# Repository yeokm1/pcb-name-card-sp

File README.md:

# pcb-name-card-sp

My name or business card that is on a Printed Circuit Board (PCB). Comes with an white LED, UV LED and a ruler. Not forgetting a QR code containing my contact details in [Vcard](https://en.wikipedia.org/wiki/VCard) format. This is an update to my [previous version](https://github.com/yeokm1/pcb-name-card) since I have changed my company.

### PCB Design software and addons/references used

1. Eagle 8.0.2
2. Modified CR2032 library based on [here](https://github.com/nickaknudson/eagle-nickaknudson/blob/master/cr2032.lbr)
2. Elecrow Design Rule Check for 2 layers (in repo as `Elecrow_2-layer_eagle_rule.dru`)
3. Elecrow Gerber Generater 2-layer board (in repo as `Elecrow_Gerber_Generater_DrillAlign.cam`)
4. QR code generated from [here](http://goqr.me/)

### Schematic drawings

Image are exported from Eagle at 600dpi.

The board schematic as seen in Eagle. The connections are slightly convoluted to prevent the traces from crossing in the board layout.

### Bill of Materials (BOM) for components only

Assume minimum order 10 pieces, cost in Singapore dollars. There are additional savings if I order more say 50 units but the savings are still small. Delivery for BOM not included.

The BOM is available in the odt spreadsheets in this repo.

### PCB fabrication

PCB fabrication is currently done by [Elecrow (10-pieces-link)](http://www.elecrow.com/10pcs-2-layer-pcb-p-1175.html) or [(50-pieces-link)](http://www.elecrow.com/50pcs-2-layer-pcb-enig-p-1172.html) based on the following settings. Remember to consult the order submission specifications at the bottom of the previous link before submitting. Use the provided Gerber generator to produce the Gerber files.

#### My Fabrication Settings:

1. Layer: 2
2. PCB Thickness: 0.6mm
3. Copper Weight : 1oz 35um (NA for 50 pieces)
4. PCB Size : 10cm Max * 10cm Max (or 50cm2 for 50 pieces)
5. PCB Color : Blue
6. Surface Finish: ENIG
7. PCB Stencil : NO Stencil
8. Lead time : Shipped in 4 to 7 days (NA for 50 pieces)
9. Panelizing : Single PCB with milling

# References
1. [How to design a 13.56 MHz
customized tag antenna](http://www.st.com/st-web-ui/static/active/jp/resource/technical/document/application_note/CD00221490.pdf)
2. [The impact of high pulse drain on CR2032 coin-cell battery capacity](http://m.eet.com/media/1121454/c0924post.pdf)
3. [Panasonic NFC Design Navigator](http://www.semicon.panasonic.co.jp/en/tool/nfcdesignnavigator/)

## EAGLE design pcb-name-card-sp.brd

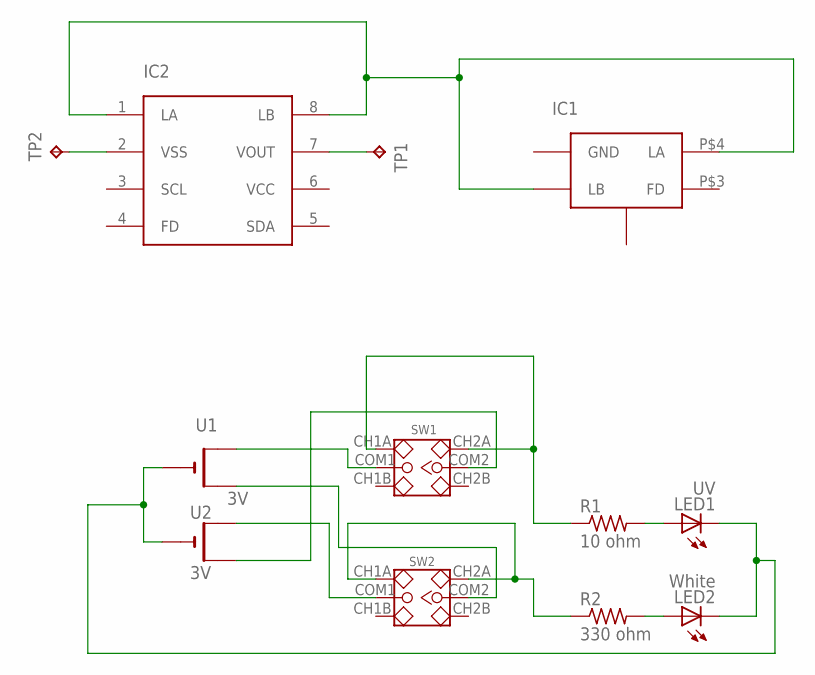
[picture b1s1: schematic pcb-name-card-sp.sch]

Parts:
IC1: NTAG21XFDRC-FIT; HXSON4-SMALL
IC2: NT3H1X01W0FTT; TSSOP-8
LED1: UV; PLCC2
LED2: White; PLCC2
R1: 10 ohm; R2010
R2: 330 ohm; R2010
SW1, SW2: SMD-TOGGLE-SWITCH-2CH(2X3P-7X3.5MM); SW6-2.54-SMD-7.0X3.5X1.5MM
TP1: VOUT; B2,54
TP2: GND; B2,54
U1, U2: 3V; CR2032-SMD

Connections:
unnamed: LED1.A, R1.2
unnamed: LED2.A, R2.2
unnamed: R2.1, SW2.CH1A, SW2.CH2A
unnamed: IC1.P$2 (LB), IC1.P$4 (LA), IC2.1 (LA), IC2.8 (LB)
unnamed: LED1.C, LED2.C, U1.-, U2.-
unnamed: SW1.COM1, U1.+$1 (+)
unnamed: IC2.2 (VSS), TP2.TP
unnamed: IC2.7 (VOUT), TP1.TP
unnamed: SW2.COM1, U2.+$1 (+)
unnamed: SW2.COM2, U1.+$2 (+1)
unnamed: SW1.COM2, U2.+$2 (+1)
unnamed: R1.1, SW1.CH1A, SW1.CH2A

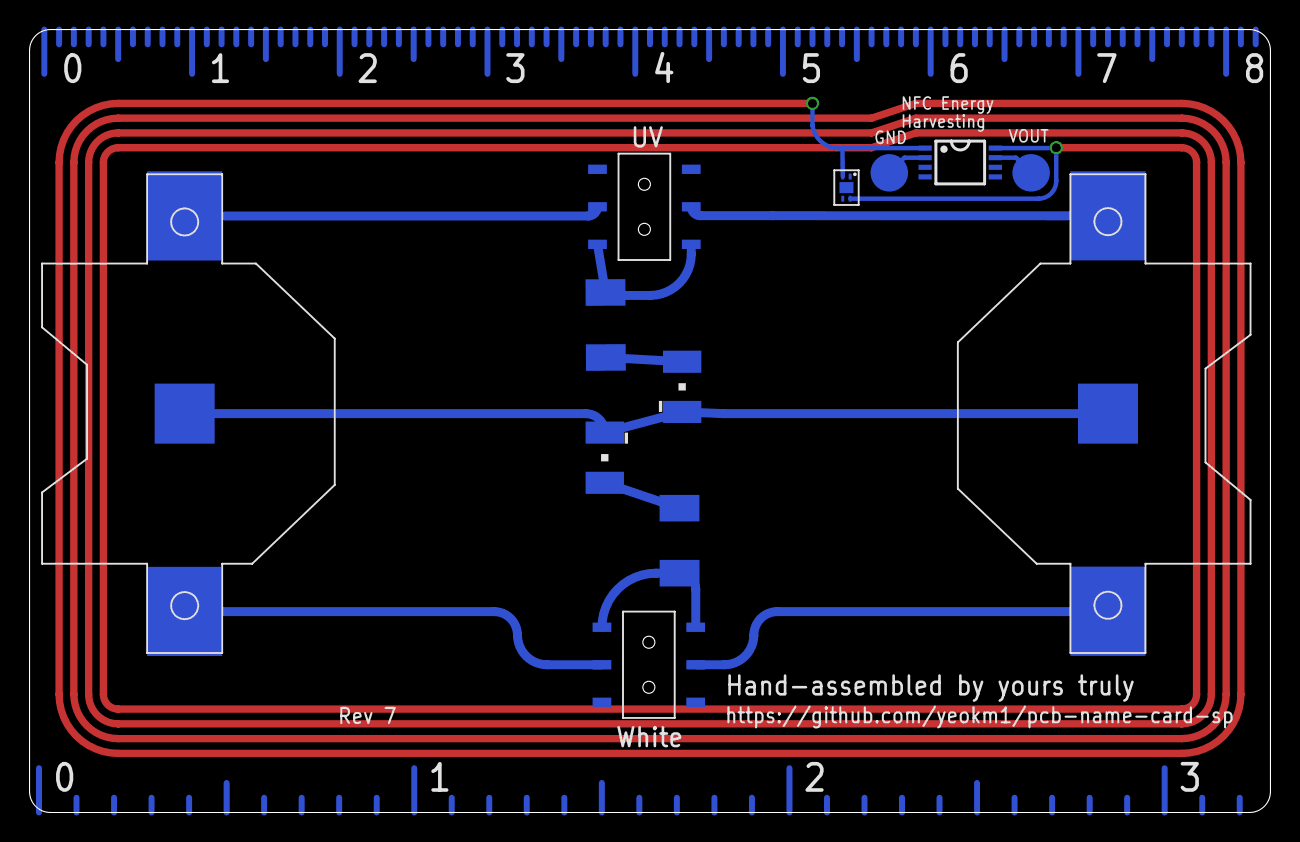
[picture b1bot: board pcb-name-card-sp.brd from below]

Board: 2 copper layers, 84.0 x 53.0 mm, 12 parts (12 on the bottom side), 12 nets.

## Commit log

2017-02-18 new card rebranded design
2017-02-18 show all layers
2017-02-18 rev2 gerber
2017-02-21 Adjusted logo position
2017-02-21 rev3 gerber
2017-02-28 add www to spgroup url
2017-03-02 rev5 moves close to actual sp card
2017-03-11 readme with new image
2017-05-17 slides
2018-08-11 update new job title
2018-08-11 change to spdigital logo
2018-08-11 update to SP Digital
2018-08-20 adjusted font sizes
2018-08-25 new version images
